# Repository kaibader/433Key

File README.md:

# LoRa Breakout Board for RFM95/RFM96 and SX1276/SX1278 Modules

This repository contains KiCad design files for a breadboard-friendly breakout board that supports various LoRa modules, such as the **HopeRF RFM95/RFM96** or Semtech **SX1276/SX1278**-based modules like the HPD13A and G-NiceRF LoRa1276-C1.

## Features

| Top View | Bottom View |
| -------- | ----------- |
|  |  |

- Supports **HopeRF RFM95/RFM96** and other pin-compatible LoRa modules.
- Designed to fit standard breadboards for easy prototyping.
- Simple SPI-based communication with microcontrollers.

## Schematic Overview

The breakout board includes the following key components and connections:

### 1. **LoRa Module**
   - This module, based on the SX1276 transceiver, handles LoRa communication at 868 MHz or 915 MHz.
   - It communicates with the microcontroller via the **SPI interface** (SCK, MOSI, MISO, NSS pins).
   - Additional **DIO pins (DIO0-DIO5)** are exposed, allowing the module to send interrupts or general-purpose I/O signals.
   - **Antenna**: The RFM9x is connected to an external antenna via an SMA connector for wireless communication.

### 2. **SPI Interface**
   - The SPI interface is used to connect the RFM9x to a microcontroller, with signals for **MISO, MOSI, SCK, NSS (SEL)**, and a **RESET** pin.
   - This enables the module to send and receive data through standard SPI communication.

### 3. **DIO Pin Connector**
   - The board provides access to the **DIO0-DIO5 pins**, which are general-purpose input/output pins for signaling and interrupt control. These can be connected to a microcontroller for event-driven handling of LoRa transmissions.

### 4. **Antenna Connection (SMA)**
   - The **SMA connector** is used to attach an external antenna, which is crucial for enabling long-range LoRa communication.

### 5. **Power Supply and Decoupling Capacitors**
   - The board operates at **+3.3V** and includes two decoupling capacitors:
     - **C1 (100nF)** and **C2 (4.7uF)** help filter out noise and stabilize the power supply to ensure proper operation of the LoRa module.
   - These capacitors prevent voltage fluctuations from affecting the module's performance, especially during transmission.

### 6. **Reset Circuit**
   - The **RESET pin** is connected to a 100k pull-up resistor **(R2)**, and another 100k resistor **(R1)** is used to control the accessibility (via **SEL**) of the module.
   - This allows external control for reinitializing the module as needed.

## Pin-Compatible LoRa Modules

This breakout board is designed to be compatible with the **HopeRF RFM9x** series and the following pin-compatible alternatives:

1. **HopeRF RFM95** (by HopeRF):
   - A widely used LoRa transceiver module that supports long-range, low-power wireless communication.
   - **Manufacturer**: [HopeRF](https://www.hoperf.com).

2. **HPD13A** (by HPD Technology):
   - A pin-compatible and shielded alternative to the RFM95, based on the SX1276 transceiver.
   - **Manufacturer**: [HPD Technology](http://www.hpdtek.com).

3. **G-NiceRF LoRa1276-C1** (by NiceRF):
   - A pin-compatible module using the same SX1276 chip as the HPD13A, designed for similar wireless communication applications.
   - **Manufacturer**: [NiceRF](https://www.nicerf.com).

Feel free to inform me about other alternatives that are available and pin-compatible.

## License

This project is licensed under the **Creative Commons Attribution 4.0 International (CC BY 4.0)**. See the [LICENSE](https://creativecommons.org/licenses/by/4.0/) page for details.

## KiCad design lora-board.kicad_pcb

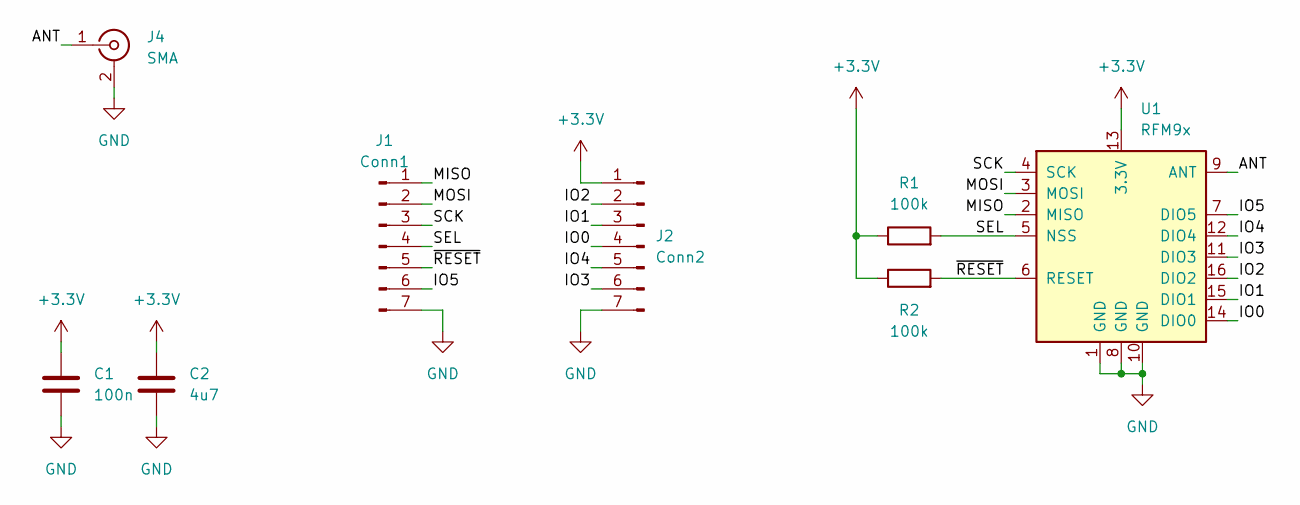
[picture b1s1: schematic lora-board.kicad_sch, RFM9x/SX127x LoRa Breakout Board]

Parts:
C1: 100n; C_0603_1608Metric_Pad1.08x0.95mm_HandSolder
C2: 4u7; C_0603_1608Metric_Pad1.08x0.95mm_HandSolder
J1: Conn1; PinHeader_1x07_P2.54mm_Vertical
J2: Conn2; PinHeader_1x07_P2.54mm_Vertical
J4: SMA; SMA_Samtec_SMA-J-P-H-ST-EM1_EdgeMount
R1, R2: 100k; R_0603_1608Metric_Pad0.98x0.95mm_HandSolder
U1: RFM9x; HOPERF_RFM9XW_SMD

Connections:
+3.3V: C1.1, C2.1, J2.1, R1.1, R2.1, U1.13 (3.3V)
/ANT: J4.1 (In), U1.9 (ANT)
/IO0: J2.4, U1.14 (DIO0)
/IO1: J2.3, U1.15 (DIO1)
/IO2: J2.2, U1.16 (DIO2)
/IO3: J2.6, U1.11 (DIO3)
/IO4: J2.5, U1.12 (DIO4)
/IO5: J1.6, U1.7 (DIO5)
/MISO: J1.1, U1.2 (MISO)
/MOSI: J1.2, U1.3 (MOSI)
/SCK: J1.3, U1.4 (SCK)
/SEL: J1.4, R1.2, U1.5 (NSS)
/~RESET: J1.5, R2.2, U1.6 (RESET)
GND: C1.2, C2.2, J1.7, J2.7, J4.2 (Ext), U1.1 (GND), U1.8 (GND), U1.10 (GND)

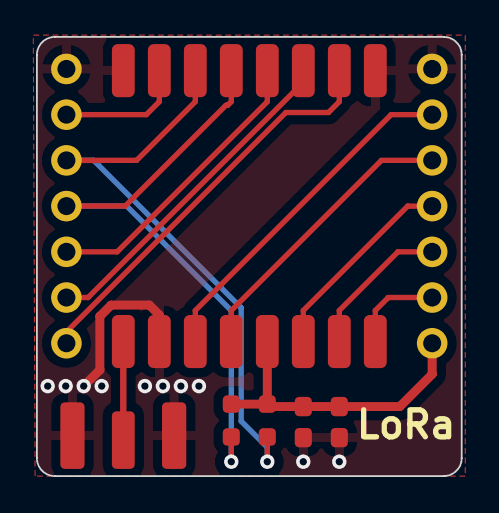
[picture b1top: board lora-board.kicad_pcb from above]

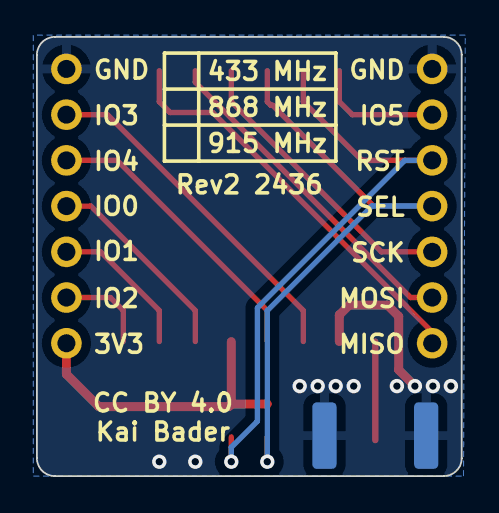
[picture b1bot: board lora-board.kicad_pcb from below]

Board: 2 copper layers, 23.6 x 24.4 mm, 8 parts (2 on the bottom side), 14 nets.

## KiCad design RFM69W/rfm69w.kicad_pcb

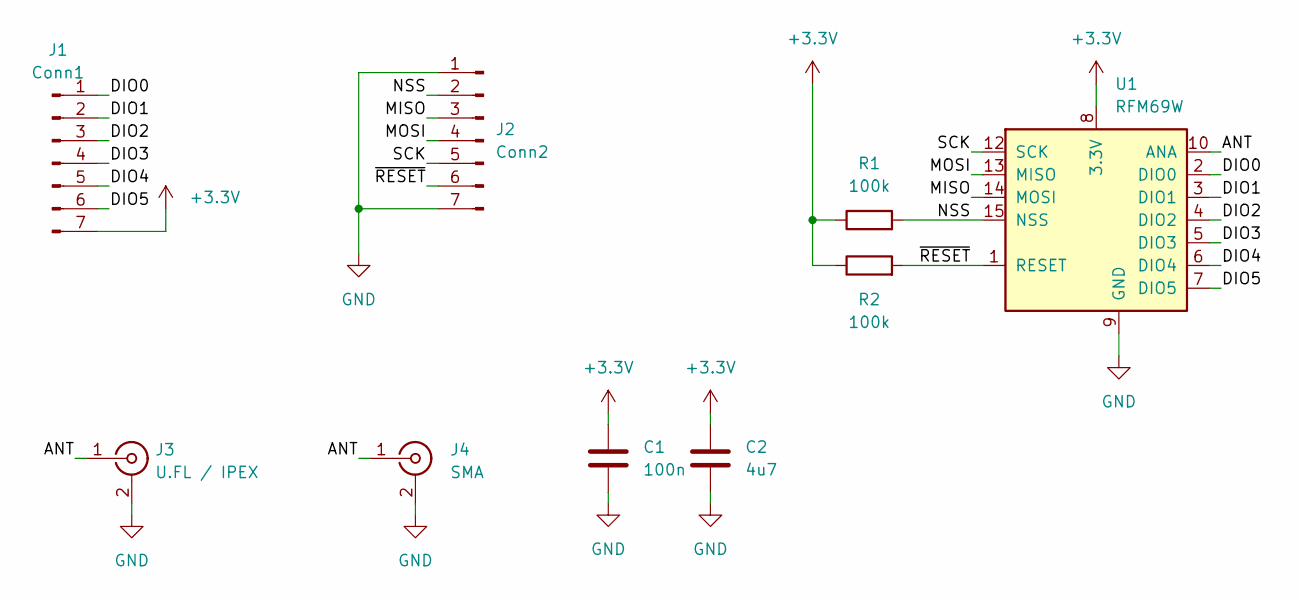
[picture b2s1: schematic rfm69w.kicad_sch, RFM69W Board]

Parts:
C1: 100n; C_0603_1608Metric_Pad1.08x0.95mm_HandSolder
C2: 4u7; C_0603_1608Metric_Pad1.08x0.95mm_HandSolder
J1: Conn1; PinHeader_1x07_P2.54mm_Vertical
J2: Conn2; PinHeader_1x07_P2.54mm_Vertical
J3: U.FL / IPEX; U.FL_Molex_MCRF_73412-0110_Vertical
J4: SMA; SMA_Samtec_SMA-J-P-X-ST-EM1_EdgeMount
R1, R2: 100k; R_0603_1608Metric_Pad0.98x0.95mm_HandSolder
U1: RFM69W; HOPERF_RFM69HW

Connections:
+3.3V: C1.1, C2.1, J1.7, R1.1, R2.1, U1.8 (3.3V)
/ANT: J3.1 (In), J4.1 (In), U1.10 (ANA)
/DIO0: J1.1, U1.2 (DIO0)
/DIO1: J1.2, U1.3 (DIO1)
/DIO2: J1.3, U1.4 (DIO2)
/DIO3: J1.4, U1.5 (DIO3)
/DIO4: J1.5, U1.6 (DIO4)
/DIO5: J1.6, U1.7 (DIO5)
/MISO: J2.3, U1.14 (MOSI)
/MOSI: J2.4, U1.13 (MISO)
/NSS: J2.2, R1.2, U1.15 (NSS)
/SCK: J2.5, U1.12 (SCK)
/~RESET: J2.6, R2.2, U1.1 (RESET)
GND: C1.2, C2.2, J2.1, J2.7, J3.2 (Ext), J4.2 (Ext), U1.9 (GND), U1.11 (GND)

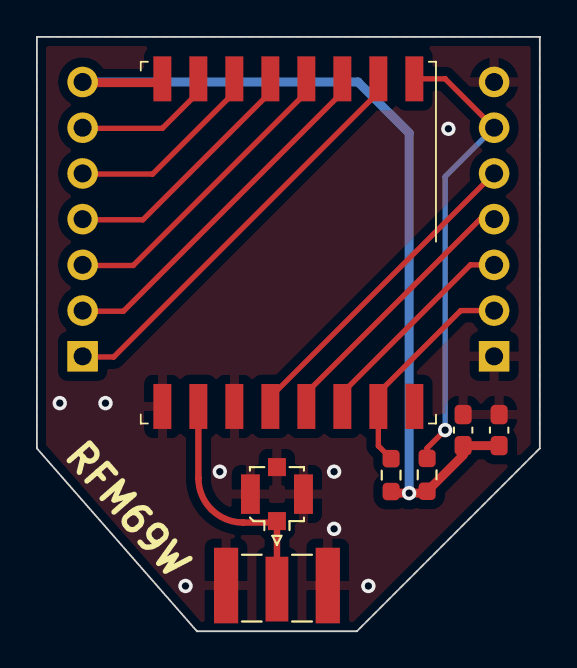
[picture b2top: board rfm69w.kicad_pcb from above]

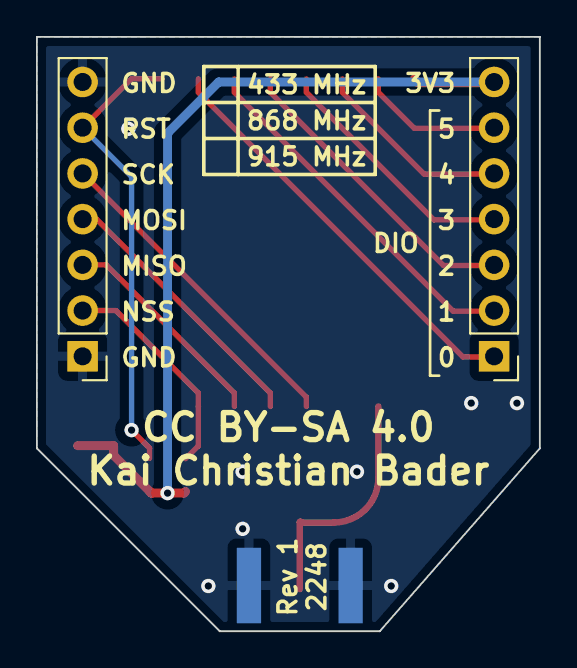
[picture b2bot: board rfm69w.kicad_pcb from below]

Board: 2 copper layers, 27.9 x 33.0 mm, 9 parts (2 on the bottom side), 14 nets.

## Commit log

2013-10-22 Initial commit. Created an ignore list.
2015-10-11 Added files for the RFM12 Breakout Board.
2015-10-11 Updated the ignore list.
2015-10-11 Added Gerber files.
2015-10-11 Routed the RFM26W Breakout Board.
2015-10-11 Layout update
2015-10-11 Some clean-up.
2015-10-11 Fixed the font line width to 6 mil.
2015-10-11 Done some clean-up.
2015-10-11 Layout updates.
2015-10-11 Added a RFM26W Breakout Board design.
2017-02-09 Switched the project frame to KiCad
2017-02-09 Revert "Switched the project frame to KiCad"
2017-02-09 Clean-up
2022-11-18 Converted the RFM12 and RFM26W Breakout Board Projects from EagleCAD to KiCAD.
2022-11-18 Added Specification PDFs
2022-11-18 Renamed Specification Folder to Documentation
2022-11-27 Added RFM95/RFM96 and RFM69W Breakout Boards.
2022-12-04 Updated the RFM69W and RFM95W/RFM96W board layouts.
2022-12-04 Generated Gerber files.
2024-09-07 LoRa Breakout Board Revision 2
    - Shifted the focus of the repository towards the new LoRa breakout board design.
    - Moved the old designs into a 'Deprecated' folder.
    - Added a ReadMe (Markdown).
    - Added module documentation.
2024-09-07 Clean-up. Removed an obsolete file.
2024-09-07 Added a README for the deprecated designs.

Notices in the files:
RFM69W/rfm69w.kicad_pcb:
CC BY-SA 4.0
lora-board.kicad_sch:
License: CC BY 4.0
